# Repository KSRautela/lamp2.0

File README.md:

# IoT Analog Clock with Illuminated Control

A Wi-Fi connected wall clock that uses a 60-LED WS2812B ring to display time like traditional analog clock hands. Built with ESP32/ESP8266 running WLED firmware.

## Features

- **Analog Time Display**: LED ring shows hour, minute, and second hands
- **Wi-Fi Connected**: Automatic time sync via NTP
- **Mode Toggle**: Physical illuminated button switches between clock and party modes
- **Web Interface**: Full WLED web control for effects and settings
- **Mobile App**: Control via official WLED mobile apps

## Demo Videos

- **Clock Mode**: `lamp2.0_clockMode.mp4` - See the LED ring displaying time as analog clock hands
- **Effect Mode**: `lamp2.0_effectMode.mp4` - Watch the decorative lighting effects in action

## What's Included

- **PCB Design**: KiCad files for custom control board
- **3D Models**: STL files for case components
- **Laser Cuts**: DXF/SVG files for mounting plates
- **Gerber Files**: Ready for PCB manufacturing
- **Documentation**: Complete build and setup guides

## Quick Start

1. **Hardware**: Follow `HARDWARE.md` for component list and wiring
2. **Software**: See `SOFTWARE.md` for WLED setup and configuration
3. **Resources**: Check `RESOURCES.md` for download links and tools

## Project Structure

```
├── pcb/                    # KiCad PCB design files
├── 3dPrints/              # STL files for 3D printed parts
├── laserCuts/             # DXF/SVG files for laser cutting
├── gerber.zip             # PCB manufacturing files
├── lamp2.0_clockMode.mp4  # Demo video - Clock mode
├── lamp2.0_effectMode.mp4 # Demo video - Effect mode
├── HARDWARE.md            # Component list and assembly guide
├── SOFTWARE.md            # WLED configuration and setup
└── RESOURCES.md           # Download links and resources
```

## How It Works

The clock uses a 60-LED ring where each LED represents a position on a traditional clock face. The ESP32/ESP8266 connects to Wi-Fi, fetches accurate time via NTP, and illuminates LEDs to show:

- **Hour Hand**: Group of LEDs pointing to current hour
- **Minute Hand**: LED(s) indicating current minute  
- **Second Hand**: Single LED sweeping around the ring

Press the illuminated button to toggle between clock mode and decorative lighting effects.

## License

Open source hardware and software project. See individual component licenses in documentation.

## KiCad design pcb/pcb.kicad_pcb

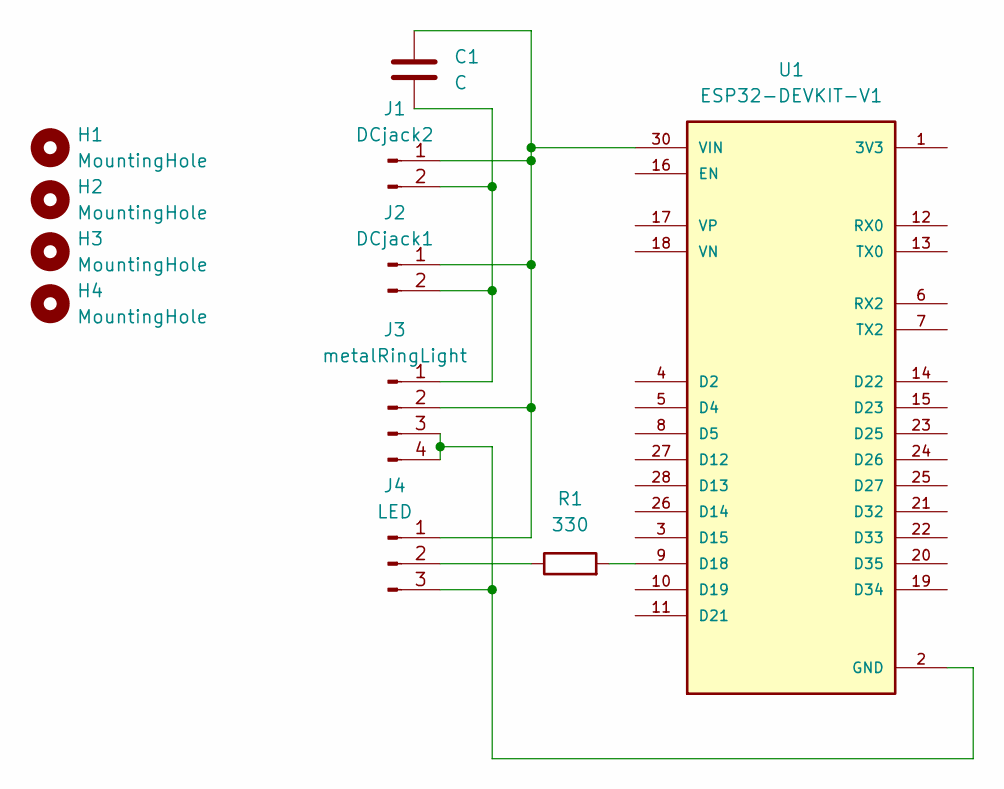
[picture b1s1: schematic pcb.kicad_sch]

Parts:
C1: C; C_Disc_D5.0mm_W2.5mm_P2.50mm
H1, H2, H3, H4: MountingHole; MountingHole_2.2mm_M2
J1: DCjack2; PinSocket_1x02_P2.54mm_Vertical
J2: DCjack1; PinSocket_1x02_P2.54mm_Vertical
J3: metalRingLight; PinSocket_1x04_P2.54mm_Vertical
J4: LED; PinSocket_1x03_P2.54mm_Vertical
R1: 330; R_Axial_DIN0204_L3.6mm_D1.6mm_P5.08mm_Horizontal
U1: ESP32-DEVKIT-V1; MODULE_ESP32_DEVKIT_V1; PARTREV N/A

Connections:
GND: J3.3, J3.4, J4.3, U1.2 (GND), U1.29 (GND)
unnamed: C1.2, J1.1, J2.1, J3.2, J4.1, U1.30 (VIN)
unnamed: C1.1, J1.2, J2.2, J3.1
unnamed: J4.2, R1.1
unnamed: R1.2, U1.9 (D18)

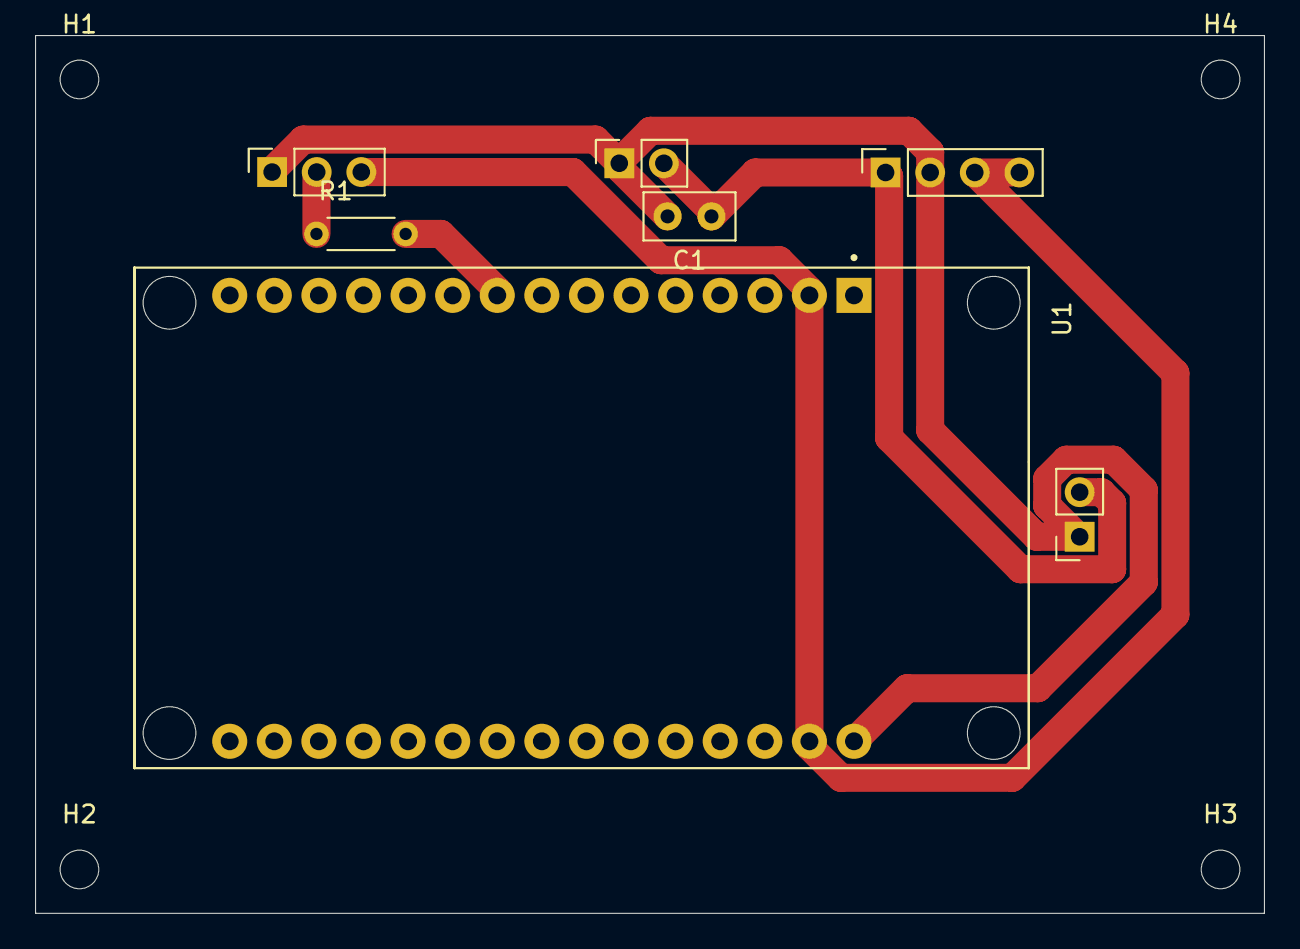
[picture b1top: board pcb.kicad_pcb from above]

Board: 2 copper layers, 70.0 x 50.0 mm, 11 parts (0 on the bottom side), 5 nets.

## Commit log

2026-01-21 Initial commit: Lamp 2.0 hardware project
2026-01-21 Add comprehensive hardware and software documentation
2026-01-21 Add comprehensive resources guide and improve mobile app documentation
2026-01-21 Add M2 threaded inserts to hardware BOM for PCB mounting
2026-01-21 Add M3 washers to hardware BOM
2026-01-21 Update PCB design files and add latest backup
2026-01-21 Add demonstration videos showing clock mode and effect mode
2026-01-21 Add comprehensive README with demo video references
